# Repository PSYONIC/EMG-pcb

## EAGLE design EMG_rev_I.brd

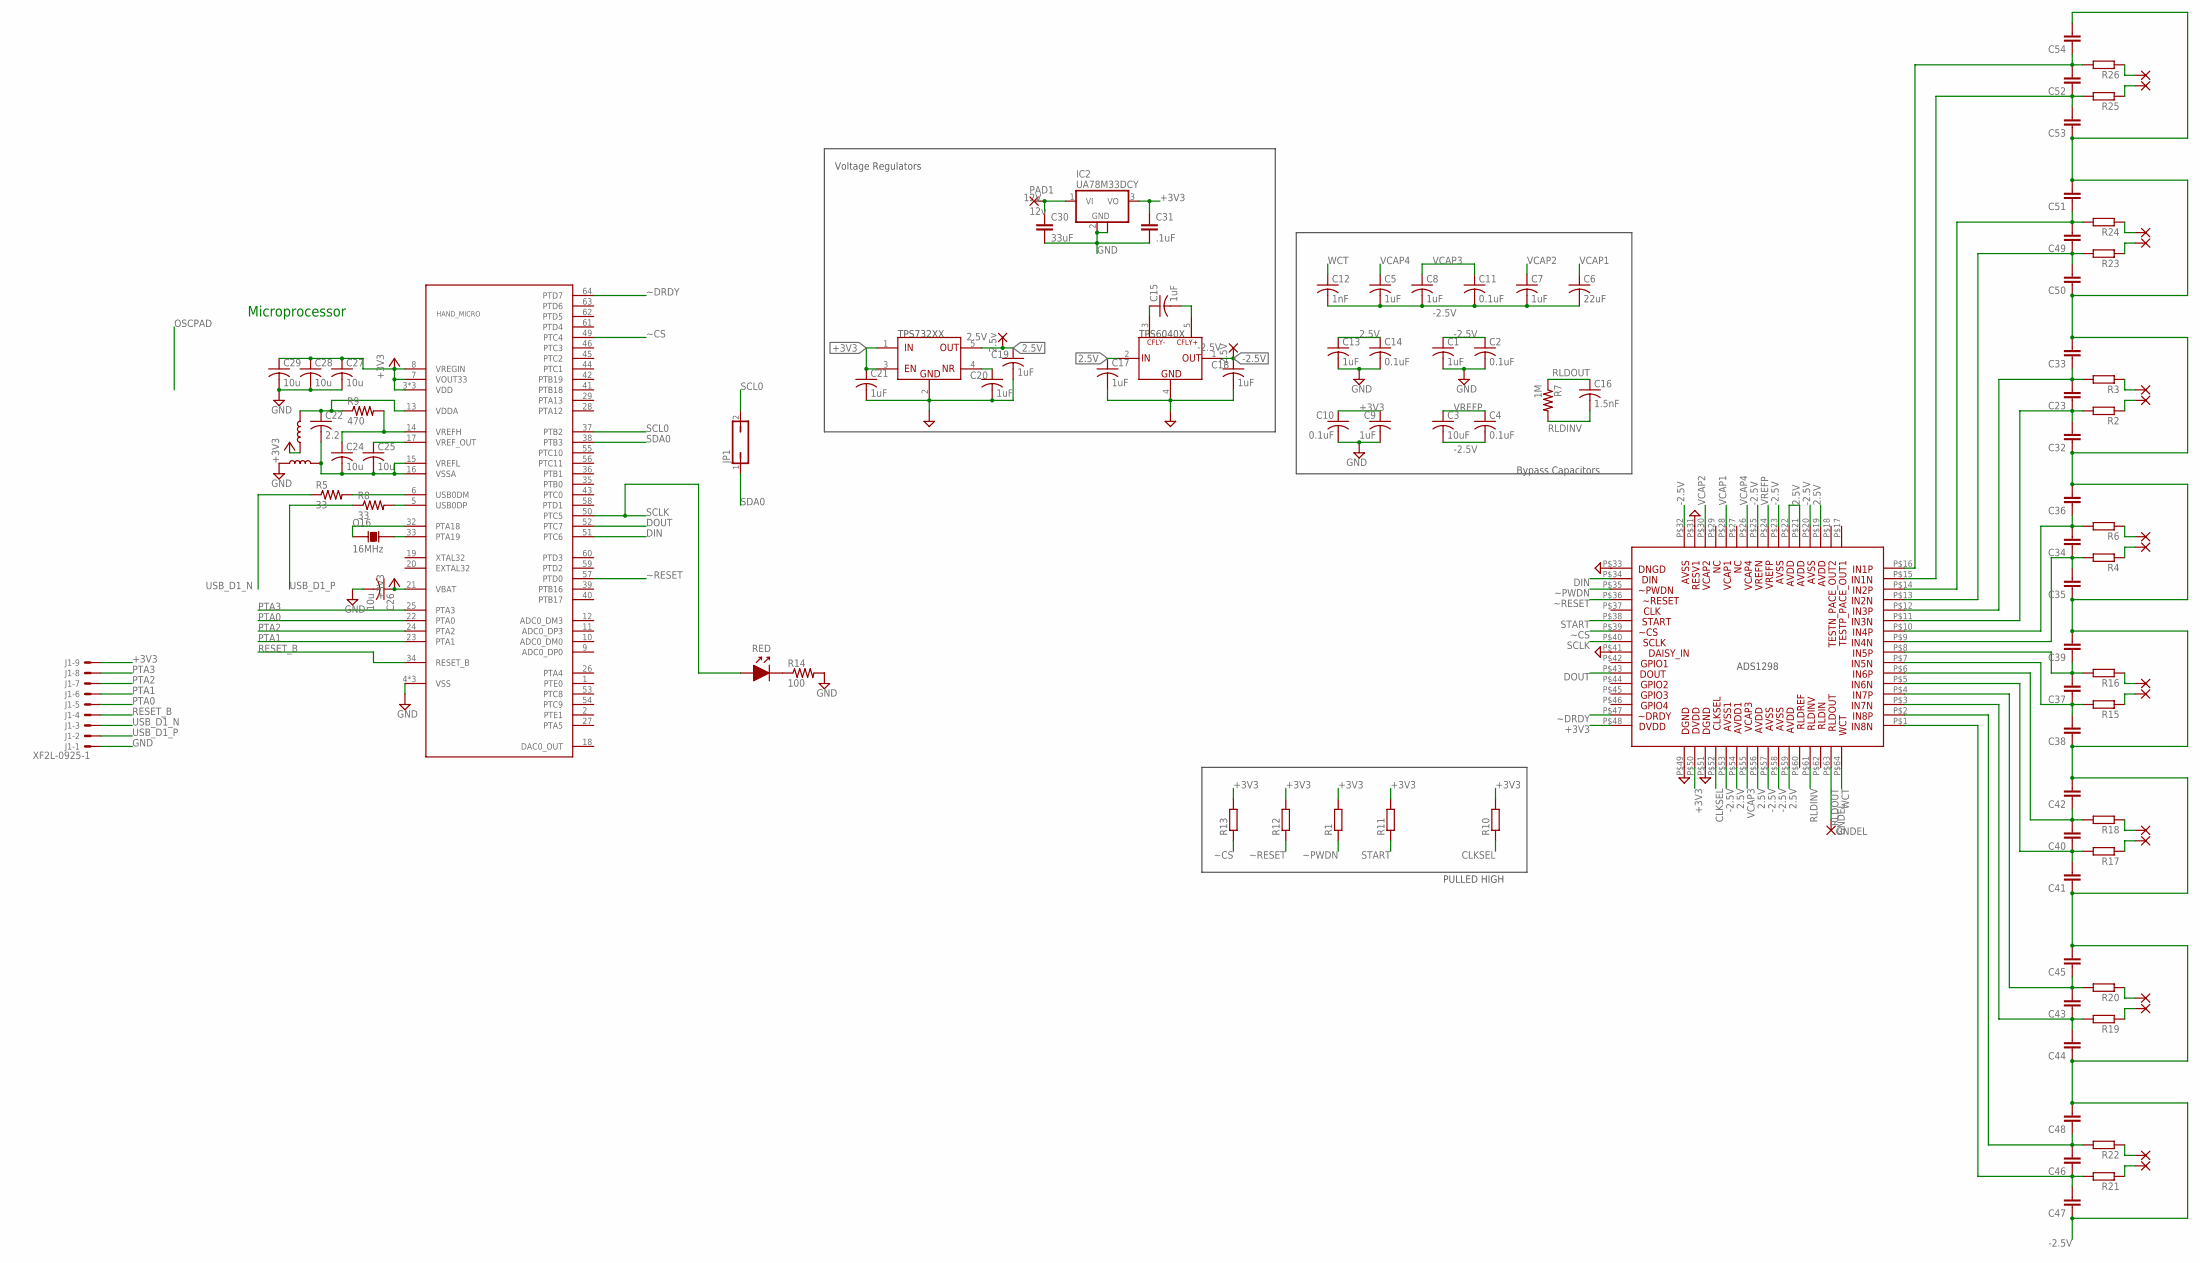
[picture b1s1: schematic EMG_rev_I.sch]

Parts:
2.5V: 2.5v; 2,54/0,9
-2.5V: -2.5V; 2,54/0,9
C1, C5, C7, C8, C9, C13, C15, C17, C18, C19, C20, C21: 1uF; C0603
C2, C4, C10, C11, C14: 0.1uF; C0603
C3: 10uF; C0603
C6: 22uF; C0603
C12: 1nF; C0603
C16: 1.5nF; C0603
C22: 2.2; C0402
C23, C32, C33, C34, C35, C36, C37, C38, C39, C40, C41, C42, C43, C44, C45, C46, C47, C48, C49, C50, C51, C52, C53, C54: CC0402; C0402
C24, C25, C26, C27, C28, C29: 10u; C0402
C30: 33uF; C0402
C31: .1uF; C0402
GNDEL: GNDEL; 2,54/0,9
HAND_MICRO: MK20DX256VLH7; LQFP-64-10-10
IC2: UA78M33DCY; SOT223
J1: XF2L-0925-1
JP1: JP1Q; JP1
O16: 16MHz; NX3225SA
PAD1: 12v; 2,54/0,9
R1, R2, R3, R4, R6, R10, R11, R12, R13, R15, R16, R17, R18, R19, R20, R21, R22, R23, R24, R25, R26: RR0402; R0402
R5, R8: 33; R0402
R7: 1M; R0603
R9: 470; R0402
R14: 100; R0603
RED: LED0603; L0603
U$1: ADS1298; TQFP-64
U$2, U$13: FERRITE600OHM100MHZ; L0603
U$3: TPS6040X; SOT23-5
U$4: TPS732XX; SOT23-5
U$12, U$14, U$15, U$16, U$17, U$18, U$19, U$20: 2X1,6/0,9

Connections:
2.5V: 2.5V.1, C13.1, C14.1, C17.1, C19.1, U$1.P$19, U$1.P$21, U$1.P$22, U$1.P$54, U$1.P$56, U$1.P$59, U$3.2 (IN), U$4.5 (OUT)
12V: C30.1, IC2.1 (VI), PAD1.1
+3V3: C9.1, C10.1, C21.1, C26.1, C27.1, C28.1, C29.1, C31.1, HAND_MICRO.3 (VDD), HAND_MICRO.7 (VOUT33), HAND_MICRO.8 (VREGIN), HAND_MICRO.21 (VBAT), HAND_MICRO.30 (VDD), HAND_MICRO.48 (VDD), IC2.3 (VO), J1.9 (MS), R1.2, R10.2, R11.2, R12.2, R13.2, U$1.P$48, U$1.P$50, U$4.1 (IN), U$4.3 (EN), U$13.1
-2.5V: -2.5V.1, C1.1, C2.1, C3.2, C4.2, C5.2, C6.2, C7.2, C8.2, C11.2, C12.2, C18.1, C32.1, C33.2, C35.1, C36.2, C38.1, C39.2, C41.1, C42.2, C44.1, C45.2, C47.1, C48.2, C50.1, C51.2, C53.1, C54.2, U$1.P$20, U$1.P$23, U$1.P$25, U$1.P$32, U$1.P$53, U$1.P$57, U$1.P$58, U$3.1 (OUT)
CLKSEL: R10.1, U$1.P$52
DIN: HAND_MICRO.51 (PTC6), U$1.P$34
DOUT: HAND_MICRO.52 (PTC7), U$1.P$43
GND: C1.2, C2.2, C9.2, C10.2, C13.2, C14.2, C17.2, C18.2, C19.2, C20.2, C21.2, C26.2, C27.2, C28.2, C29.2, C30.2, C31.2, HAND_MICRO.4 (VSS), HAND_MICRO.31 (VSS), HAND_MICRO.47 (VSS), IC2.2 (GND), IC2.4 (GND), J1.1 (MSV), R14.2, U$1.P$31, U$1.P$33, U$1.P$41, U$1.P$49, U$1.P$51, U$2.1, U$3.4 (GND), U$4.2 (GND)
unnamed: R3.1, U$12.2 (P1)
unnamed: R2.1, U$12.1
unnamed: C15.1, U$3.3 (CFLY-)
unnamed: C15.2, U$3.5 (CFLY+)
unnamed: C20.1, U$4.4 (NR)
unnamed: C22.2, C24.2, C25.2, HAND_MICRO.15 (VREFL), HAND_MICRO.16 (VSSA), U$2.2
unnamed: C22.1, HAND_MICRO.13 (VDDA), R9.1, U$13.2
unnamed: C24.1, HAND_MICRO.14 (VREFH), R9.2
unnamed: HAND_MICRO.33 (PTA19), O16.3
unnamed: R14.1, RED.2
unnamed: HAND_MICRO.32 (PTA18), O16.1
unnamed: C23.1, C32.2, R2.2, U$1.P$11
unnamed: C23.2, C33.1, R3.2, U$1.P$12
unnamed: R6.1, U$14.2 (P1)
unnamed: R4.1, U$14.1
unnamed: C25.1, HAND_MICRO.17 (VREF_OUT)
unnamed: C34.1, C35.2, R4.2, U$1.P$9
unnamed: C34.2, C36.1, R6.2, U$1.P$10
unnamed: R16.1, U$15.2 (P1)
unnamed: R15.1, U$15.1
unnamed: C37.1, C38.2, R15.2, U$1.P$7
unnamed: C37.2, C39.1, R16.2, U$1.P$8
unnamed: R18.1, U$16.2 (P1)
unnamed: R17.1, U$16.1
unnamed: C40.1, C41.2, R17.2, U$1.P$5
unnamed: C40.2, C42.1, R18.2, U$1.P$6
unnamed: R20.1, U$17.2 (P1)
unnamed: R19.1, U$17.1
unnamed: C43.1, C44.2, R19.2, U$1.P$3
unnamed: C43.2, C45.1, R20.2, U$1.P$4
unnamed: R22.1, U$18.2 (P1)
unnamed: R21.1, U$18.1
unnamed: C46.1, C47.2, R21.2, U$1.P$1
unnamed: C46.2, C48.1, R22.2, U$1.P$2
unnamed: R24.1, U$19.2 (P1)
unnamed: R23.1, U$19.1
unnamed: C49.1, C50.2, R23.2, U$1.P$13
unnamed: C49.2, C51.1, R24.2, U$1.P$14
unnamed: R26.1, U$20.2 (P1)
unnamed: R25.1, U$20.1
unnamed: C52.1, C53.2, R25.2, U$1.P$15
unnamed: C52.2, C54.1, R26.2, U$1.P$16
PTA0: HAND_MICRO.22 (PTA0), J1.5 (MS)
PTA1: HAND_MICRO.23 (PTA1), J1.6 (MS)
PTA2: HAND_MICRO.24 (PTA2), J1.7 (MS)
PTA3: HAND_MICRO.25 (PTA3), J1.8 (MS)
RESET_B: HAND_MICRO.34 (RESET_B), J1.4 (MS)
RLDINV: C16.2, R7.2, U$1.P$61
RLDOUT: C16.1, GNDEL.1, R7.1, U$1.P$63
SCL0: HAND_MICRO.37 (PTB2), JP1.2
SCLK: HAND_MICRO.50 (PTC5), RED.1, U$1.P$40
SDA0: HAND_MICRO.38 (PTB3), JP1.1
START: R11.1, U$1.P$38
USB_D1_N: J1.3 (MS), R5.1
USB_D1_P: J1.2 (MS), R8.1
USB_D2_N: HAND_MICRO.6 (USB0DM), R5.2
USB_D2_P: HAND_MICRO.5 (USB0DP), R8.2
VCAP1: C6.1, U$1.P$28
VCAP2: C7.1, U$1.P$30
VCAP3: C8.1, C11.1, U$1.P$55
VCAP4: C5.1, U$1.P$26
VREFP: C3.1, C4.1, U$1.P$24
WCT: C12.1, U$1.P$64
~CS: HAND_MICRO.49 (PTC4), R13.1, U$1.P$39
~DRDY: HAND_MICRO.64 (PTD7), U$1.P$47
~PWDN: R1.1, U$1.P$35
~RESET: HAND_MICRO.57 (PTD0), R12.1, U$1.P$36

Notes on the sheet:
Bypass Capacitors
PULLED HIGH
Voltage Regulators
Microprocessor

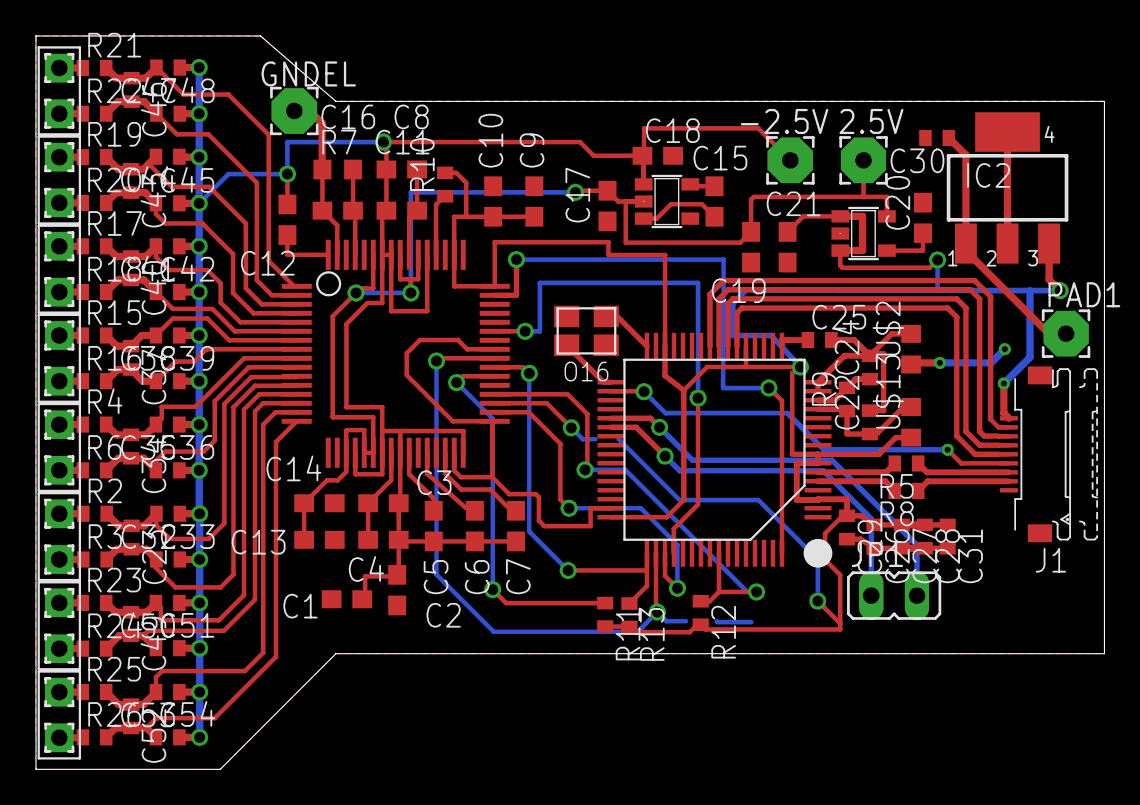
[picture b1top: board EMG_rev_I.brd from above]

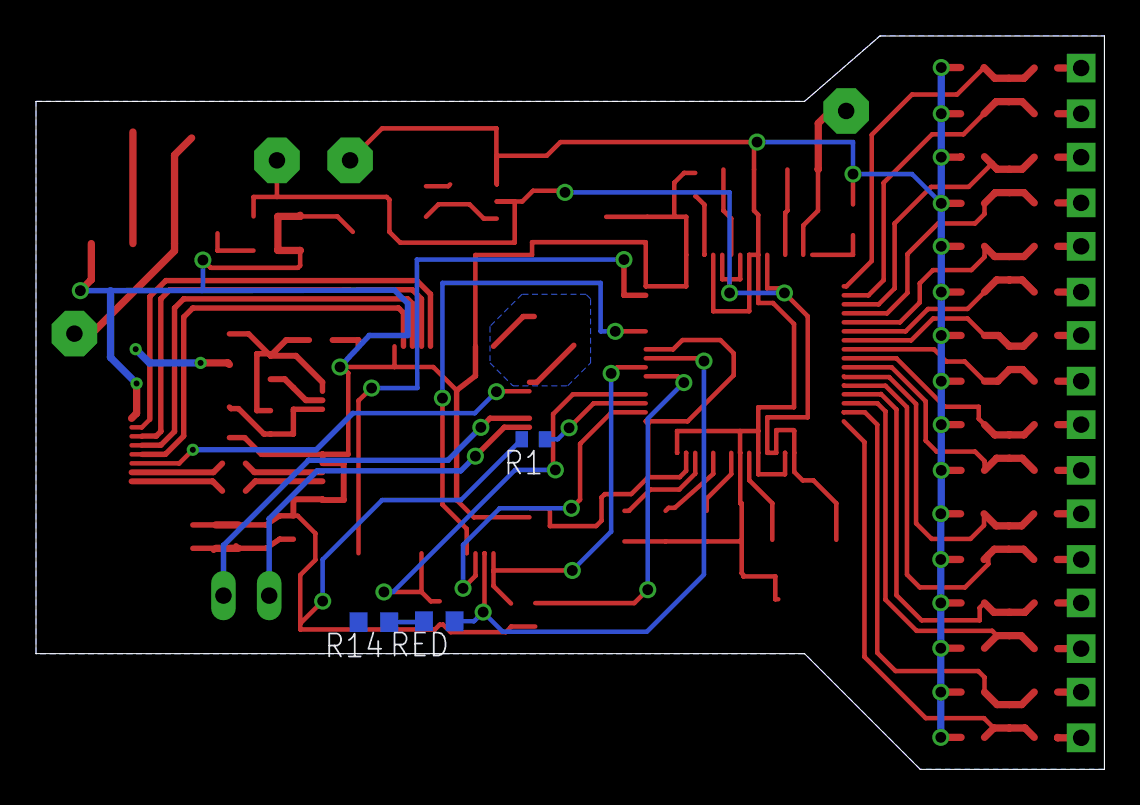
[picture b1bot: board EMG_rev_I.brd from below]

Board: 2 copper layers, 59.4 x 40.7 mm, 103 parts (3 on the bottom side), 75 nets.

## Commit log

2016-10-07 first
    first commit
